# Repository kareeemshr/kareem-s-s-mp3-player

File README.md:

# kareem-s-s-mp3-player
believe it or not its an mp3 player

heres the schematic:

heres the pcb:

heres a 3d render of the pcb:

|part|ammount|value|link|foot print|
|:----|:-------:|:----:|----|----|
|Capacitor|4|1uF|https://jlcpcb.com/partdetail/53938-CL05A105KA5NQNC/C52923|0402|
|capacitor|7|10uF|https://jlcpcb.com/partdetail/20411-CL10A106KP8NNNC/C19702|0603|
|capacitor|2|33pF|https://jlcpcb.com/partdetail/1914-0402CG330J500NT/C1562|0402|
|resistor|2|5.1K|https://jlcpcb.com/partdetail/26648-0402WGF5101TCE/C25905|0402|
|resistor|2|1K|https://jlcpcb.com/partdetail/12256-0402WGF1001TCE/C11702|0402|
|resistor|1|10K|https://jlcpcb.com/partdetail/26487-0402WGF1002TCE/C25744|0402|
|resistor|2|33| |0402|
|push button|6||https://jlcpcb.com/partdetail/XUNPU-TS_1088AR02016/C720477|SW_Push_SPST_NO_Alps_SKRK|
|usb-c input|1||https://jlcpcb.com/partdetail/Korean_HropartsElec-TYPE_C_31_M12/C165948|USB_C_Receptacle_HRO_TYPE-C-31-M-12|
|MCU(rp 2040)|1||https://jlcpcb.com/partdetail/RaspberryPi-RP2040/C2040|QFN-56-1EP_7x7mm_P0.4mm_EP3.2x3.2mm|
|flash mem(W25Q16JVSS)|1|16MB|https://jlcpcb.com/partdetail/WinbondElec-W25Q16JVSSIQ/C131025|SOIC-8_5.3x5.3mm_P1.27mm|
|LOD(MCP1700x-330xxTT)|1|5.5V inpt 3.3V outp|https://jlcpcb.com/partdetail/MSKSEMI-MCP1700T_3302E_TT_MS/C20627188|SOT-23|
|crystal|1|12MHZ|https://jlcpcb.com/partdetail/NDK-NX3225GA_12MHZ_STD_CRG2/C481407|Crystal_SMD_3225-4Pin_3.2x2.5mm|
|OLED|1|0.96|https://jlcpcb.com/partdetail/HS-HS96L03W2C03/C5248080|just use a generic conn to act as the i2c pins|
|pcm5102A|1| |https://jlcpcb.com/partdetail/TexasInstruments-PCM5102APW/C1520792|PCM5102A|
|micro sd card reader|1| |https://jlcpcb.com/partdetail/MyAntenna-A_MicroTF_185A/C22467599|Micro_SD_Card_Det_Hirose_DM3AT|
|head_phone_jack|1|https://jlcpcb.com/partdetail/Korean_HropartsElec-PJ_320B3A/C707224|PJ-320B|

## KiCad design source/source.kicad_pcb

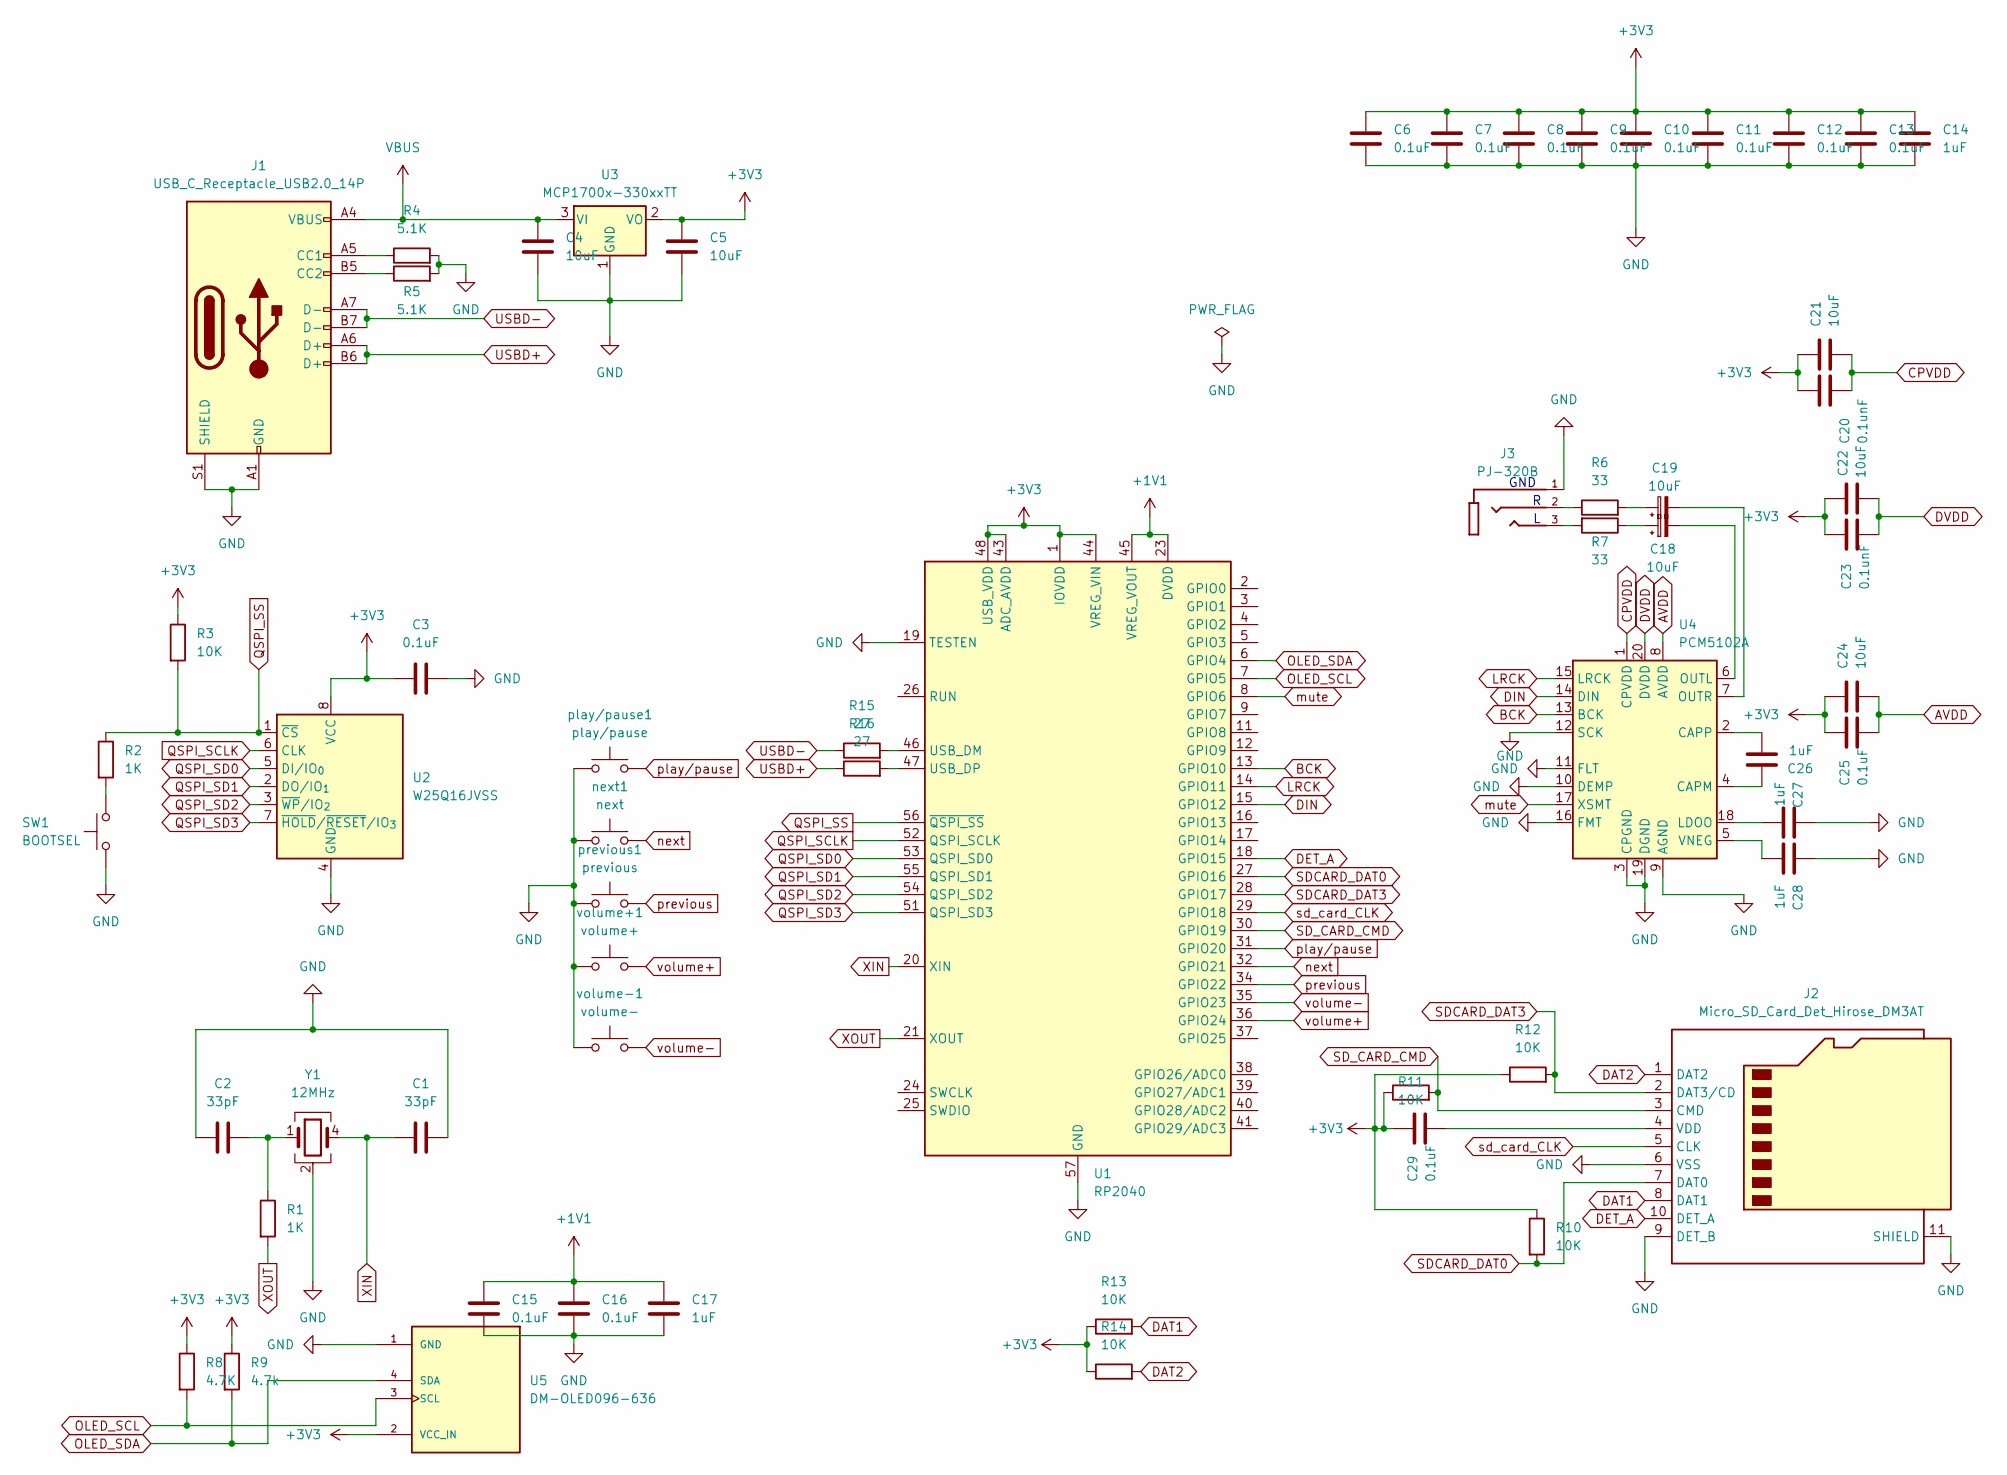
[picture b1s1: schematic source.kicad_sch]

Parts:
C1, C2: 33pF; C_0402_1005Metric
C3, C6, C7, C8, C9, C10, C11, C12, C13, C15, C16, C25, C29: 0.1uF; C_0402_1005Metric
C4, C5, C18, C19, C21, C22, C24: 10uF; C_0402_1005Metric
C14, C17, C26, C27, C28: 1uF; C_0402_1005Metric
C20, C23: 0.1unF; C_0402_1005Metric
J1: USB_C_Receptacle_USB2.0_14P; USB_C_Receptacle_HRO_TYPE-C-31-M-12
J2: Micro_SD_Card_Det_Hirose_DM3AT; microSD_HC_Hirose_DM3AT-SF-PEJM5
J3: PJ-320B; BOOMELE_PJ-320B
R1, R2: 1K; R_0402_1005Metric
R3, R10, R11, R12, R13, R14: 10K; R_0402_1005Metric
R4, R5: 5.1K; R_0402_1005Metric
R6, R7: 33; R_0402_1005Metric
R8: 4.7K; R_0402_1005Metric
R9: 4.7k; R_0402_1005Metric
R15, R16: 27; R_0402_1005Metric
SW1: BOOTSEL; SW_Push_SPST_NO_Alps_SKRK
U1: RP2040; QFN-56-1EP_7x7mm_P0.4mm_EP3.2x3.2mm
U2: W25Q16JVSS; SOIC-8_5.3x5.3mm_P1.27mm
U3: MCP1700x-330xxTT; SOT-23
U4: PCM5102A; TSSOP-20_4.4x6.5mm_P0.65mm
U5: DM-OLED096-636; MODULE_DM-OLED096-636; PARTREV 2018-09-10
Y1: 12MHz; Crystal_SMD_3225-4Pin_3.2x2.5mm
next1: next; SW_Push_SPST_NO_Alps_SKRK
play/pause1: play/pause; SW_Push_SPST_NO_Alps_SKRK
previous1: previous; SW_Push_SPST_NO_Alps_SKRK
volume+1: volume+; SW_Push_SPST_NO_Alps_SKRK
volume-1: volume-; SW_Push_SPST_NO_Alps_SKRK

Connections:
+1V1: C15.1, C16.1, C17.1, U1.23 (DVDD), U1.45 (VREG_VOUT), U1.50 (DVDD)
+3V3: C3.1, C5.1, C6.1, C7.1, C8.1, C9.1, C10.1, C11.1, C12.1, C13.1, C14.1, C20.1, C21.1, C22.1, C23.1, C24.1, C25.1, C29.1, R3.1, R8.1, R9.1, R10.1, R11.1, R12.1, R13.1, R14.1, U1.1 (IOVDD), U1.10 (IOVDD), U1.22 (IOVDD), U1.33 (IOVDD), U1.42 (IOVDD), U1.43 (ADC_AVDD), U1.44 (VREG_VIN), U1.48 (USB_VDD), U1.49 (IOVDD), U2.8 (VCC), U3.2 (VO), U5.2 (VCC_IN)
AVDD: C24.2, C25.2, U4.8 (AVDD)
BCK: U1.13 (GPIO10), U4.13 (BCK)
CPVDD: C20.2, C21.2, U4.1 (CPVDD)
DAT1: J2.8 (DAT1), R13.2
DAT2: J2.1 (DAT2), R14.2
DET_A: J2.10 (DET_A), U1.18 (GPIO15)
DIN: U1.15 (GPIO12), U4.14 (DIN)
DVDD: C22.2, C23.2, U4.20 (DVDD)
GND: C1.2, C2.1, C3.2, C4.2, C5.2, C6.2, C7.2, C8.2, C9.2, C10.2, C11.2, C12.2, C13.2, C14.2, C15.2, C16.2, C17.2, C27.1, C28.1, J1.A1 (GND), J1.A12 (GND), J1.B1 (GND), J1.B12 (GND), J1.S1 (SHIELD), J2.6 (VSS), J2.9 (DET_B), J2.11 (SHIELD), J3.1, R4.2, R5.2, SW1.1, U1.19 (TESTEN), U1.57 (GND), U2.4 (GND), U3.1 (GND), U4.3 (CPGND), U4.9 (AGND), U4.10 (DEMP), U4.11 (FLT), U4.12 (SCK), U4.16 (FMT), U4.19 (DGND), U5.1 (GND), Y1.2 (G), Y1.3 (G), next1.1, play/pause1.1, previous1.1, volume+1.1, volume-1.1; also elsewhere on the board
LRCK: U1.14 (GPIO11), U4.15 (LRCK)
unnamed: C2.2, R1.1, Y1.1
unnamed: C18.1, R7.1
unnamed: C19.1, R6.2
unnamed: J1.A5 (CC1), R4.1
unnamed: J1.B5 (CC2), R5.1
unnamed: C29.2, J2.4 (VDD)
unnamed: J3.2, R6.1
unnamed: J3.3, R7.2
unnamed 20: R2.2, SW1.2; also elsewhere on the board
unnamed: R15.2, U1.46 (USB_DM)
unnamed: R16.2, U1.47 (USB_DP)
unnamed: C26.1, U4.4 (CAPM)
unnamed: C26.2, U4.2 (CAPP)
unnamed: C27.2, U4.18 (LDOO)
unnamed: C18.2, U4.6 (OUTL)
unnamed: C19.2, U4.7 (OUTR)
unnamed: C28.2, U4.5 (VNEG)
OLED_SCL: R8.2, U1.7 (GPIO5), U5.3 (SCL)
OLED_SDA: R9.2, U1.6 (GPIO4), U5.4 (SDA)
QSPI_SCLK: U1.52 (QSPI_SCLK), U2.6 (CLK)
QSPI_SD0: U1.53 (QSPI_SD0), U2.5 (DI/IO_{0})
QSPI_SD1: U1.55 (QSPI_SD1), U2.2 (DO/IO_{1})
QSPI_SD2: U1.54 (QSPI_SD2), U2.3 (~WP/IO_{2})
QSPI_SD3: U1.51 (QSPI_SD3), U2.7 (~HOLD/~RESET/IO_{3})
QSPI_SS: R2.1, R3.2, U1.56 (~QSPI_SS), U2.1 (~CS)
SDCARD_DAT0: J2.7 (DAT0), R10.2, U1.27 (GPIO16)
SDCARD_DAT3: J2.2 (DAT3/CD), R12.2, U1.28 (GPIO17)
SD_CARD_CMD: J2.3 (CMD), R11.2, U1.30 (GPIO19)
USBD+: J1.A6 (D+), J1.B6 (D+), R16.1
USBD-: J1.A7 (D-), J1.B7 (D-), R15.1
VBUS: C4.1, J1.A4 (VBUS), J1.A9 (VBUS), J1.B4 (VBUS), J1.B9 (VBUS), U3.3 (VI)
XIN: C1.1, U1.20 (XIN), Y1.4
XOUT: R1.2, U1.21 (XOUT)
mute: U1.8 (GPIO6), U4.17 (XSMT)
next: U1.32 (GPIO21), next1.2; also elsewhere on the board
play/pause: U1.31 (GPIO20), play/pause1.2; also elsewhere on the board
previous: U1.34 (GPIO22), previous1.2; also elsewhere on the board
sd_card_CLK: J2.5 (CLK), U1.29 (GPIO18)
volume+: U1.36 (GPIO24), volume+1.2; also elsewhere on the board
volume-: U1.35 (GPIO23), volume-1.2; also elsewhere on the board

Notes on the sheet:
GND

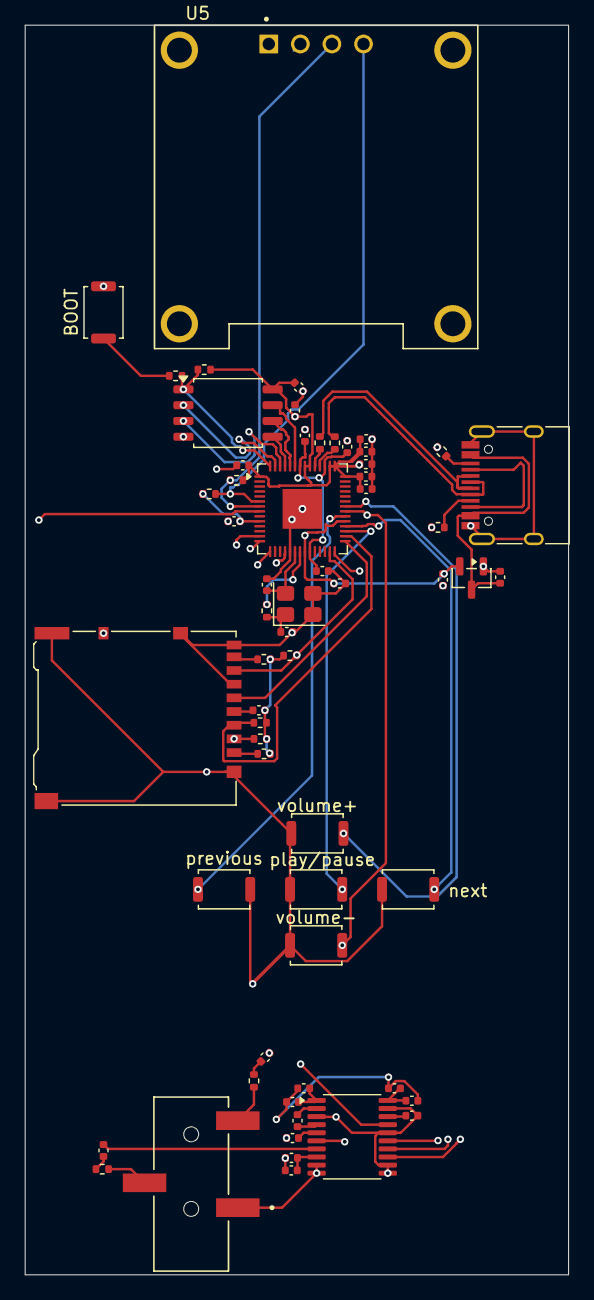
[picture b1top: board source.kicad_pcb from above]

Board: 4 copper layers, 43.7 x 100.5 mm, 60 parts (0 on the bottom side), 52 nets.

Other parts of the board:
BOOT: BOOTSEL; SW_Push_SPST_NO_Alps_SKRK
next: next; SW_Push_SPST_NO_Alps_SKRK
play/pause: play/pause; SW_Push_SPST_NO_Alps_SKRK
previous: previous; SW_Push_SPST_NO_Alps_SKRK
volume+: volume+; SW_Push_SPST_NO_Alps_SKRK
volume-: volume-; SW_Push_SPST_NO_Alps_SKRK

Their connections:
GND: BOOT.1, next.1, play/pause.1, previous.1, volume+.1, volume-.1; also elsewhere on the board
unnamed 20: BOOT.2; also elsewhere on the board
next: next.2; also elsewhere on the board
play/pause: play/pause.2; also elsewhere on the board
previous: previous.2; also elsewhere on the board
volume+: volume+.2; also elsewhere on the board
volume-: volume-.2; also elsewhere on the board

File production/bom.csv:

Designator,Footprint,Quantity,Value,LCSC Part #
BOOT,SW_Push_SPST_NO_Alps_SKRK,1,BOOTSEL,
"C1, C2",0402,2,33pF,
"C10, C11, C12, C13, C15, C16, C20, C25, C29, C3, C6, C7, C8, C9",0402,14,0.1uF,
"C14, C17, C26, C27, C28",0402,5,1uF,
"C18, C19, C21, C22, C24, C4, C5",0402,7,10uF,
C23,0402,1,0.1unF,
J1,USB_C_Receptacle_HRO_TYPE-C-31-M-12,1,USB_C_Receptacle_USB2.0_14P,
J2,microSD_HC_Hirose_DM3AT-SF-PEJM5,1,Micro_SD_Card_Det_Hirose_DM3AT,
J3,BOOMELE_PJ-320B,1,PJ-320B,
NEXT,SW_Push_SPST_NO_Alps_SKRK,1,next,
PLAY/PAUSE,SW_Push_SPST_NO_Alps_SKRK,1,play/pause,
PREVIOUS,SW_Push_SPST_NO_Alps_SKRK,1,previous,
"R1, R2",0402,2,1K,
"R10, R11, R12, R13, R14, R3",0402,6,10K,
"R15, R16",0402,2,27,
"R4, R5",0402,2,5.1K,
"R6, R7",0402,2,33,
"R8, R9",0402,2,4.7K,
U1,QFN-56-1EP_7x7mm_P0.4mm_EP3.2x3.2mm,1,RP2040,
U2,SOIC-8_5.3x5.3mm_P1.27mm,1,W25Q16JVSS,
U3,SOT-23,1,MCP1700x-330xxTT,
U4,TSSOP-20_4.4x6.5mm_P0.65mm,1,PCM5102A,
U5,MODULE_DM-OLED096-636,1,DM-OLED096-636,
VOLUME+,SW_Push_SPST_NO_Alps_SKRK,1,volume+,
VOLUME-,SW_Push_SPST_NO_Alps_SKRK,1,volume-,
Y1,Crystal_SMD_3225-4Pin_3.2x2.5mm,1,12MHz,

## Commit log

2026-03-28 added all the files
